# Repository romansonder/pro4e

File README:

########################################################################
# How to use git
########################################################################
First time you run git:
$ git clone https://github.com/romansonder/pro4e.git

$ git pull			# download the newest files from git

$ git add *			# select the files you want to upload
$ git commit			# write in your changes
$ git push			# upload your files to git

########################################################################
# Run the Makefiles on Windows:
########################################################################

#-----------------------------------------------------------------------
# Installation of cygwin
#-----------------------------------------------------------------------
Install cygwin from this site:
https://cygwin.com/install.html

Select a Download Site (mirror), if possible one in your country.

Select the following packages to be installed (allways newest version):

make: the Gnu version
git: Distributed version
texlive: TEX Live binaries
texlive-collection-latex
texlive-collection-latexextra
texlive-collection-langerman
texlive-collection-bibtexextra
texlive-collection-context
texlive-collection-fontsrecommended
texlive-collection-formatsextra
texlive-collection-pictures
texlive-collection-plaingeneric
texlive-collection-mathscience

#-----------------------------------------------------------------------
# Change to the Directory and run the Makefile
#-----------------------------------------------------------------------
open the cygwin terminal

clone the git repository
$ git clone http://..

change to the directory with the Makefile (use tab to autofill)
$ cd pro4e/documentation/02_technical_report/

run makefile
$ make

clean the directory from unused files
$ make clean

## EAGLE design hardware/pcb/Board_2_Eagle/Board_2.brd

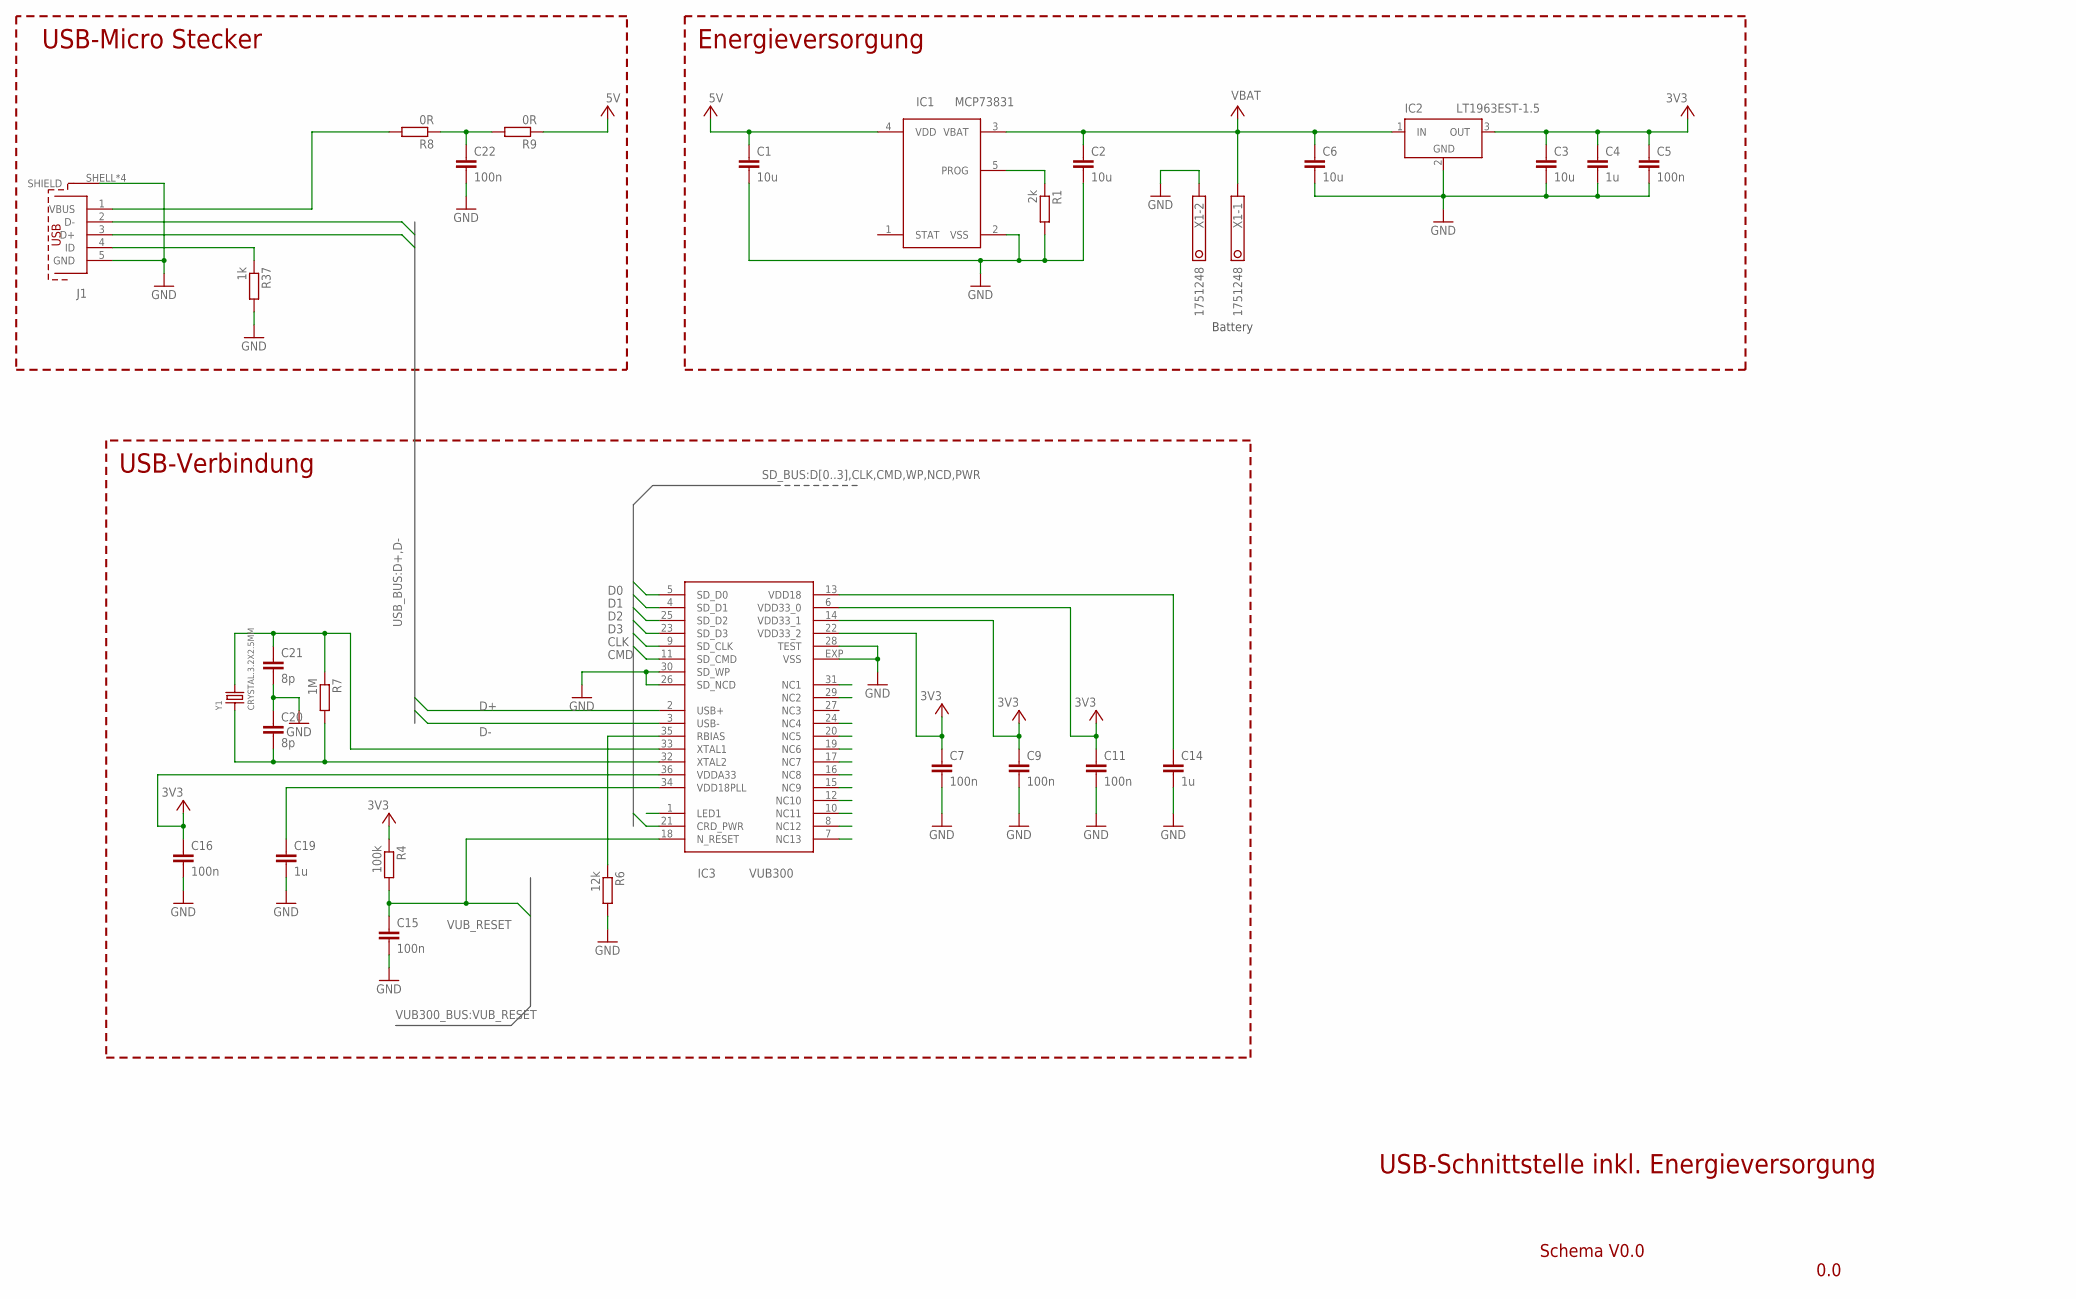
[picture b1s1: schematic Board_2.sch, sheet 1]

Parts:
C1, C2, C3, C6: 10u; C0805
C4: 1u; C0603
C5, C22: 100n; C0603
C7, C9, C11, C15, C16: 100n; C0402
C14, C19: 1u; C0402
C20, C21: 8p; C0402
IC1: MCP73831; SOT23-5
IC2: LT1963EST-1.5; SOT223
IC3: VUB300; QFN36-6X6
J1: 629105136821
R1: 2k; R0603
R4: 100k; R0402
R6: 12k; R0402
R7: 1M; R0402
R8, R9: 0R; R0603
R37: 1k; R0402
X1: 1751248
Y1: CRYSTAL.3.2X2.5MM; 3.2X2.5MM

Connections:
+3V3: C3.1, C4.1, C5.1, C7.1, C9.1, C11.1, C16.1, IC2.3 (OUT), IC3.6 (VDD33_0), IC3.14 (VDD33_1), IC3.22 (VDD33_2), IC3.36 (VDDA33), R4.1; also elsewhere on the board
+5V: C1.1, IC1.4 (VDD), R9.1
CLK: IC3.9 (SD_CLK); also elsewhere on the board
CMD: IC3.11 (SD_CMD); also elsewhere on the board
D0: IC3.5 (SD_D0); also elsewhere on the board
D1: IC3.4 (SD_D1); also elsewhere on the board
D2: IC3.25 (SD_D2); also elsewhere on the board
D3: IC3.23 (SD_D3); also elsewhere on the board
D+: IC3.2 (USB+), J1.3 (D+)
D-: IC3.3 (USB-), J1.2 (D-)
GND: C1.2, C2.2, C3.2, C4.2, C5.2, C6.2, C7.2, C9.2, C11.2, C14.2, C15.2, C16.2, C19.2, C20.1, C21.2, C22.2, IC1.2 (VSS), IC2.2 (GND), IC2.4 (GND), IC3.26 (SD_NCD), IC3.28 (TEST), IC3.30 (SD_WP), IC3.EXP (VSS), J1.5 (GND), J1.SHELL (SHIELD), J1.SHELL1 (SHIELD), J1.SHELL2 (SHIELD), J1.SHELL3 (SHIELD), R1.2, R6.2, R37.2, X1.2; also elsewhere on the board
unnamed: IC1.5 (PROG), R1.1
unnamed: J1.4 (ID), R37.1
unnamed: IC3.35 (RBIAS), R6.1
unnamed: J1.1 (VBUS), R8.2
unnamed: C20.2, IC3.32 (XTAL2), R7.2, Y1.1
unnamed: C21.1, IC3.33 (XTAL1), R7.1, Y1.3 (2)
unnamed: C22.1, R8.1, R9.2
PWR: IC3.21 (CRD_PWR); also elsewhere on the board
V+: C2.1, C6.1, IC1.3 (VBAT), IC2.1 (IN), X1.1; also elsewhere on the board
VDD18: C14.1, IC3.13 (VDD18)
VDD18PLL: C19.1, IC3.34 (VDD18PLL)
VUB_RESET: C15.1, IC3.18 (N_RESET), R4.2; also elsewhere on the board

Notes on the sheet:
Battery
USB-Micro Stecker
Energieversorgung
USB-Verbindung
Schema V0.0
0.0
USB-Schnittstelle inkl. Energieversorgung

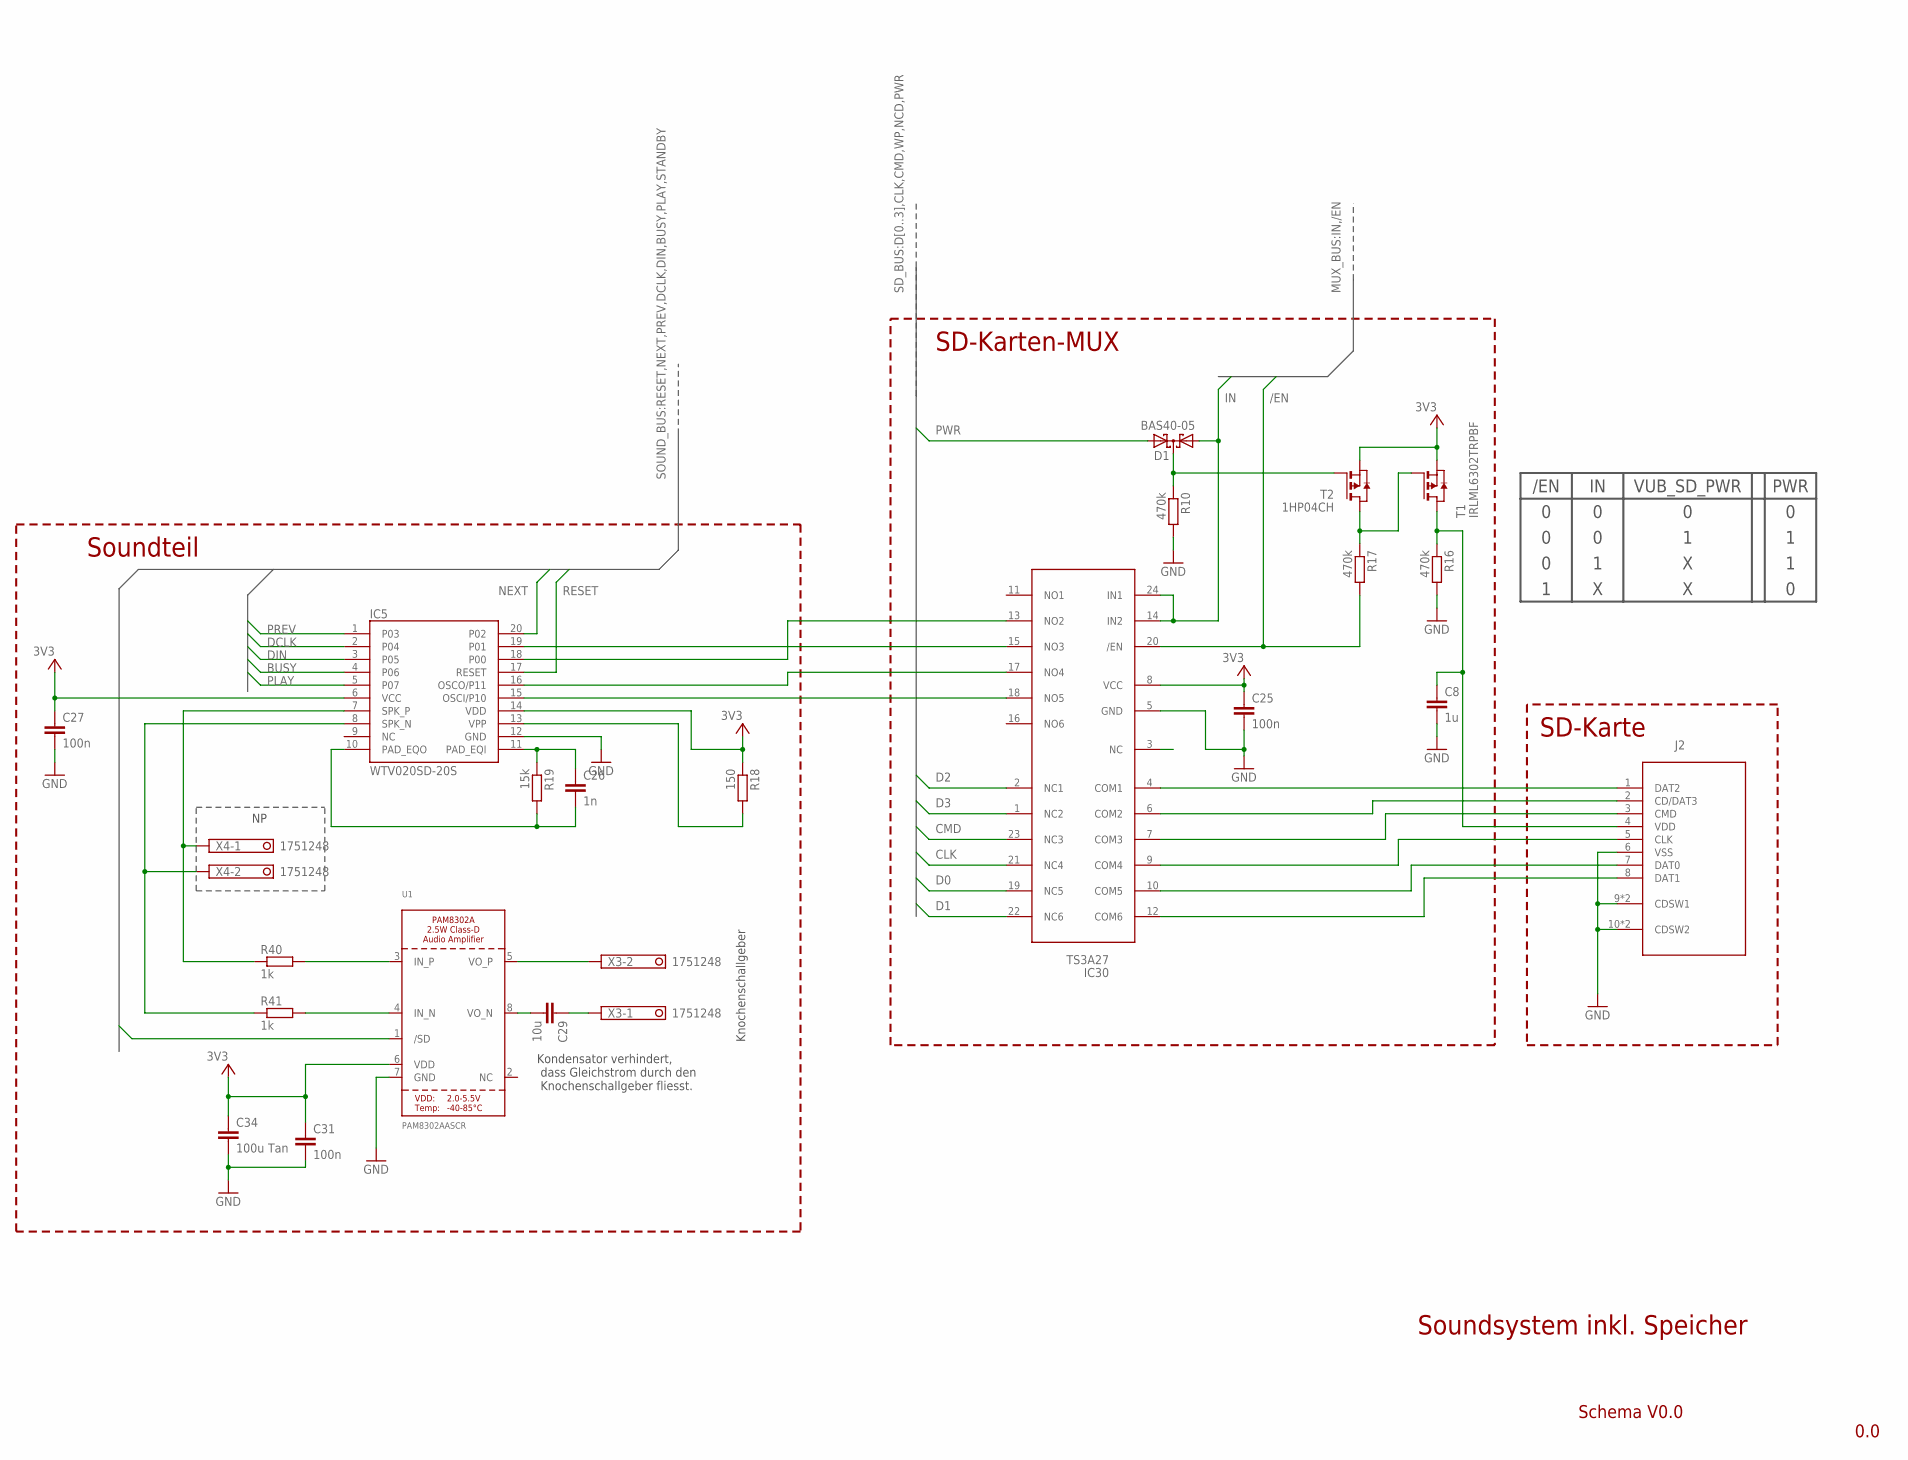
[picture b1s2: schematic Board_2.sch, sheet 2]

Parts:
C8: 1u; C0603
C25, C31: 100n; C0603
C26: 1n; C0402
C27: 100n; C0402
C29: 10u; C0603
C34: 100u Tan; C1206
D1: BAS40-05; SOT23
IC5: WTV020SD-20S; SSOP_20
IC30: TS3A27; TSSOP24
J2: 693071010811
R10, R16, R17: 470k; R0603
R18: 150; R0402
R19: 15k; R0402
R40, R41: 1k; R0402
T1: IRLML6302TRPBF; SOT-23
T2: 1HP04CH; SOT-23
U1: PAM8302AASCR; MSOP8_0.65MM
X3, X4: 1751248

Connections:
+3V3: C25.1, C27.1, C31.1, C34.1, IC5.6 (VCC), IC5.14 (VDD), IC30.8 (VCC), R18.1, T1.2 (S), T2.2 (S), U1.6 (VDD); also elsewhere on the board
/EN: IC30.20 (/EN), R17.2; also elsewhere on the board
BUSY: IC5.4 (P06); also elsewhere on the board
CLK: IC30.21 (NC4); also elsewhere on the board
CMD: IC30.23 (NC3); also elsewhere on the board
D0: IC30.19 (NC5); also elsewhere on the board
D1: IC30.22 (NC6); also elsewhere on the board
D2: IC30.2 (NC1); also elsewhere on the board
D3: IC30.1 (NC2); also elsewhere on the board
DCLK: IC5.2 (P04); also elsewhere on the board
DIN: IC5.3 (P05); also elsewhere on the board
GND: C8.2, C25.2, C27.2, C31.2, C34.2, IC5.12 (GND), IC30.5 (GND), J2.6 (VSS), J2.9 (CDSW1), J2.9-1 (CDSW1), J2.10 (CDSW2), J2.10-1 (CDSW2), R10.2, R16.2, U1.7 (GND); also elsewhere on the board
IN: D1.1 (A1), IC30.14 (IN2), IC30.24 (IN1); also elsewhere on the board
unnamed: R41.2, U1.4 (IN_N)
unnamed: IC5.19 (P01), IC30.15 (NO3)
unnamed: R40.2, U1.3 (IN_P)
unnamed: U1.5 (VO_P), X3.2
unnamed: C29.1, X3.1
unnamed: C29.2, U1.8 (VO_N)
unnamed: IC30.9 (COM4), J2.5 (CLK)
unnamed: IC5.13 (VPP), R18.2
unnamed: C26.1, IC5.11 (PAD_EQI), R19.1
unnamed: IC5.16 (OSCO/P11), IC30.17 (NO4)
unnamed: IC5.15 (OSCI/P10), IC30.18 (NO5)
unnamed: IC30.4 (COM1), J2.1 (DAT2)
unnamed: IC30.12 (COM6), J2.8 (DAT1)
unnamed: IC30.6 (COM2), J2.2 (CD/DAT3)
unnamed: R17.1, T1.3 (G), T2.1 (D)
unnamed: D1.3 (C), R10.1, T2.3 (G)
NCD1: C8.1, J2.4 (VDD), R16.1, T1.1 (D)
NEXT: IC5.20 (P02); also elsewhere on the board
PLAY: IC5.5 (P07); also elsewhere on the board
PREV: IC5.1 (P03); also elsewhere on the board
PWM: C26.2, IC5.10 (PAD_EQO), R19.2
PWR: D1.2 (A2); also elsewhere on the board
RESET: IC5.17 (RESET); also elsewhere on the board
SDCS: IC5.18 (P00), IC30.13 (NO2)
SDDI: IC30.7 (COM3), J2.3 (CMD)
SDDO: IC30.10 (COM5), J2.7 (DAT0)
SPK+: IC5.7 (SPK_P), R40.1, X4.1
SPK-: IC5.8 (SPK_N), R41.1, X4.2

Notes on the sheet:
SD-Karten-MUX
SD-Karte
Soundteil
Schema V0.0
0.0
Soundsystem inkl. Speicher
Knochenschallgeber
VUB_SD_PWR
/EN
PWR
Kondensator verhindert, dass Gleichstrom durch den Knochenschallgeber fliesst.

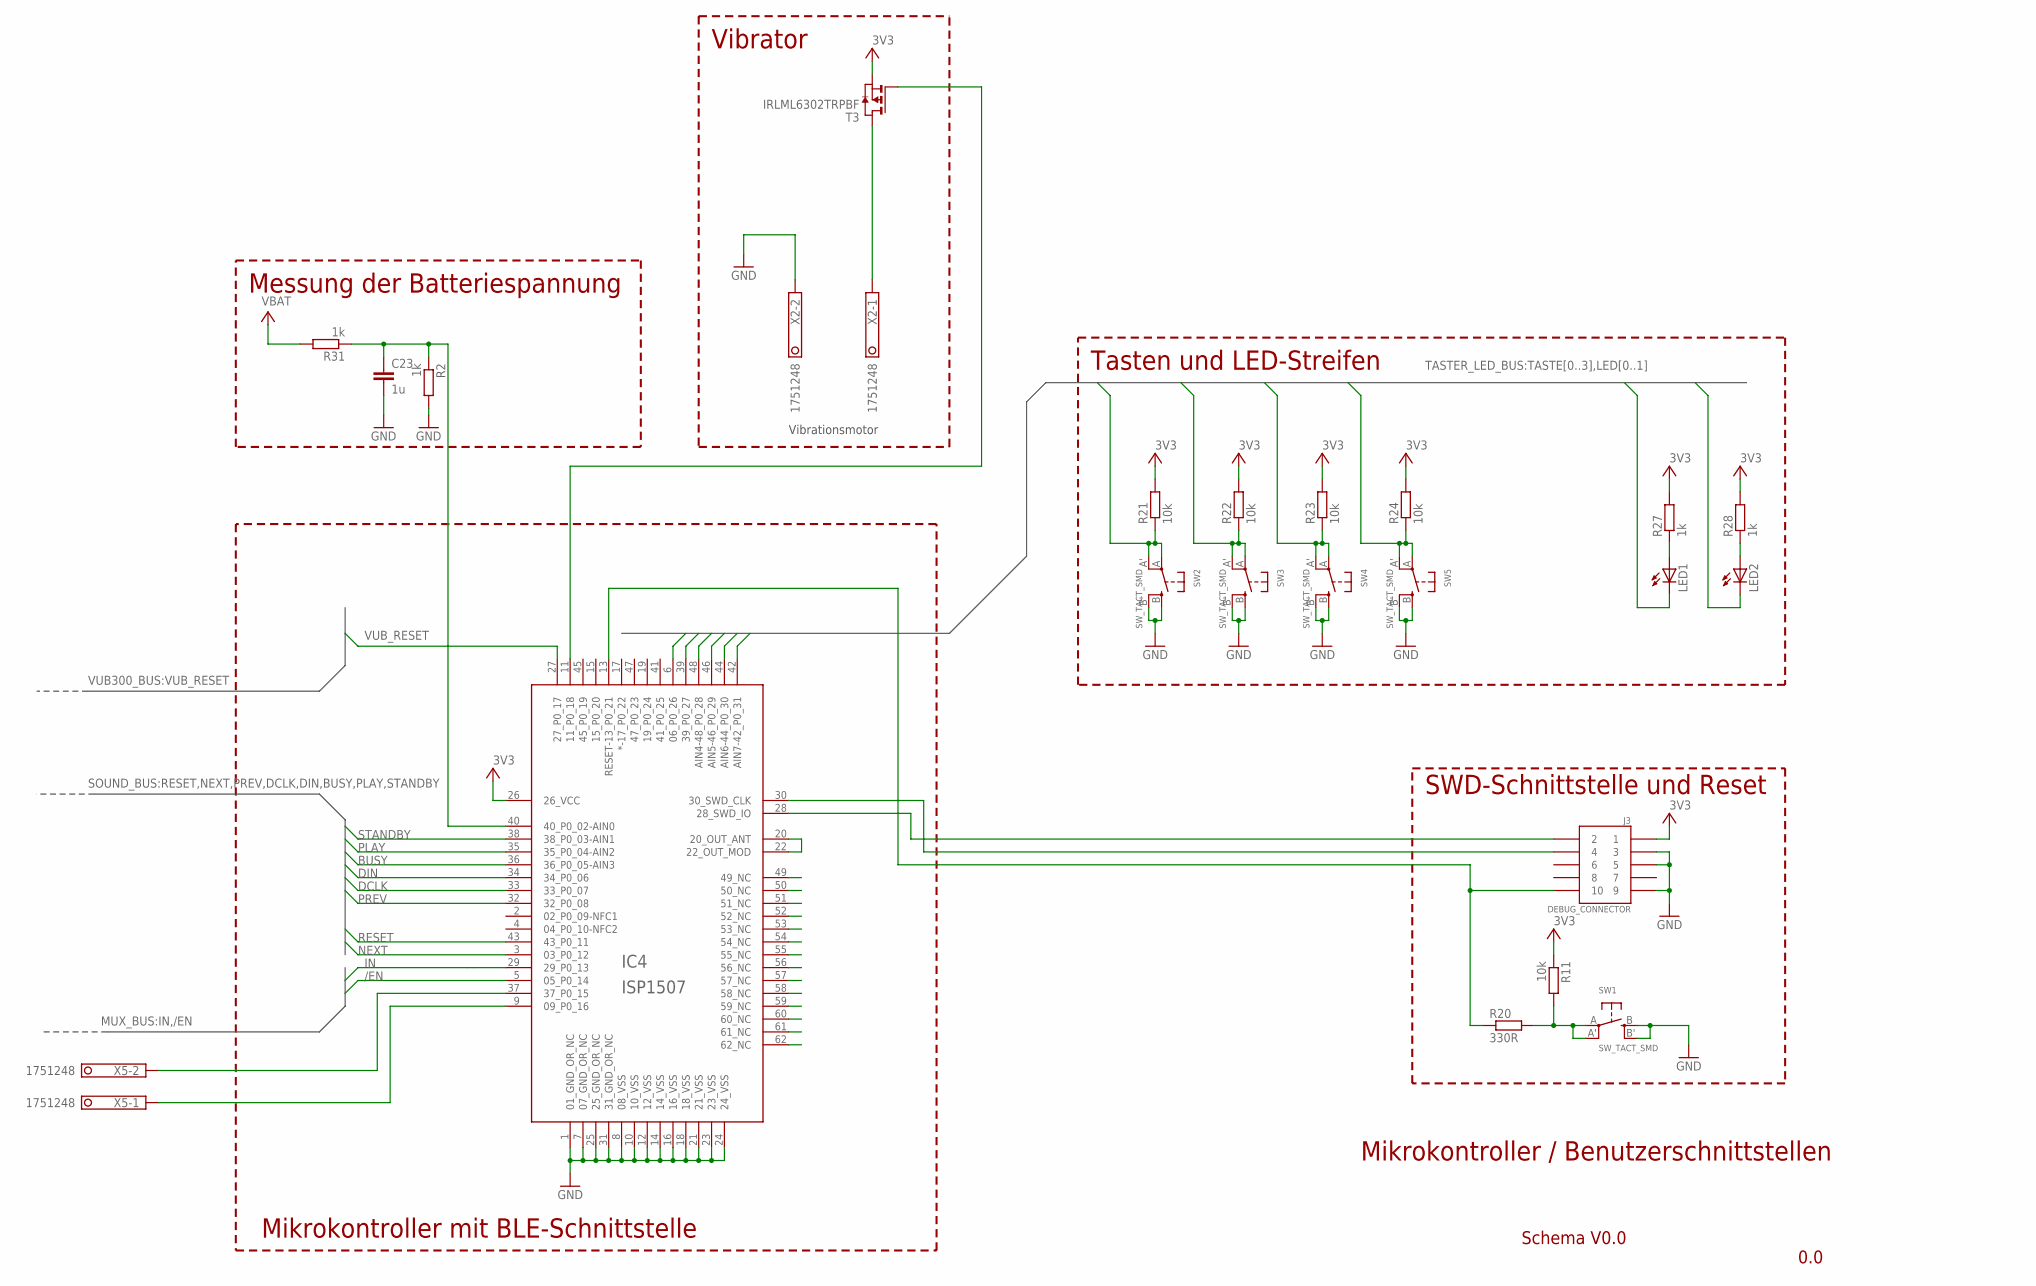
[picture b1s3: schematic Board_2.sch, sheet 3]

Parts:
C23: 1u; C0603
IC4: ISP1507
J3: DEBUG_CONNECTOR; HDRV127P5X2-10_N
LED1, LED2: LED_E; LED_1206
R2, R27, R28, R31: 1k; R0603
R11, R21, R22, R23, R24: 10k; R0603
R20: 330R; R0603
SW1, SW2, SW3, SW4, SW5: SW_TACT_SMD; EVQ-Q2
T3: IRLML6302TRPBF; SOT-23
X2, X5: 1751248

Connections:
+3V3: IC4.26 (26_VCC), J3.1, R11.1, R21.2, R22.2, R23.2, R24.2, R27.2, R28.2, T3.2 (S); also elsewhere on the board
/EN: IC4.5 (05_P0_14); also elsewhere on the board
BUSY: IC4.36 (36_P0_05-AIN3); also elsewhere on the board
DCLK: IC4.33 (33_P0_07); also elsewhere on the board
DIN: IC4.34 (34_P0_06); also elsewhere on the board
GND: C23.2, IC4.1 (01_GND_OR_NC), IC4.7 (07_GND_OR_NC), IC4.8 (08_VSS), IC4.10 (10_VSS), IC4.12 (12_VSS), IC4.14 (14_VSS), IC4.16 (16_VSS), IC4.18 (18_VSS), IC4.21 (21_VSS), IC4.23 (23_VSS), IC4.24 (24_VSS), IC4.25 (25_GND_OR_NC), IC4.31 (31_GND_OR_NC), J3.3, J3.5, J3.9, R2.2, SW1.B (S), SW1.B' (S1), SW2.B (S), SW2.B' (S1), SW3.B (S), SW3.B' (S1), SW4.B (S), SW4.B' (S1), SW5.B (S), SW5.B' (S1), X2.2; also elsewhere on the board
IN: IC4.29 (29_P0_13); also elsewhere on the board
LED0: IC4.39 (39_P0_27), LED1.C
LED1: IC4.6 (06_P0_26), LED2.C
unnamed: IC4.37 (37_P0_15), X5.2
unnamed: IC4.20 (20_OUT_ANT), IC4.22 (22_OUT_MOD)
unnamed: IC4.11 (11_P0_18), T3.3 (G)
unnamed: IC4.9 (09_P0_16), X5.1
unnamed: R11.2, R20.2, SW1.A, SW1.A' (P1)
unnamed: IC4.30 (30_SWD_CLK), J3.4
unnamed: IC4.28 (28_SWD_IO), J3.2
unnamed: LED1.A, R27.1
unnamed: C23.1, IC4.40 (40_P0_02-AIN0), R2.1, R31.1
unnamed: LED2.A, R28.1
unnamed: T3.1 (D), X2.1
unnamed: IC4.13 (RESET-13_P0_21), J3.10, R20.1
NEXT: IC4.3 (03_P0_12); also elsewhere on the board
PLAY: IC4.35 (35_P0_04-AIN2); also elsewhere on the board
PREV: IC4.32 (32_P0_08); also elsewhere on the board
RESET: IC4.43 (43_P0_11); also elsewhere on the board
STANDBY: IC4.38 (38_P0_03-AIN1)
TASTE0: IC4.42 (AIN7-42_P0_31), R21.1, SW2.A, SW2.A' (P1)
TASTE1: IC4.44 (AIN6-44_P0_30), R22.1, SW3.A, SW3.A' (P1)
TASTE2: IC4.46 (AIN5-46_P0_29), R23.1, SW4.A, SW4.A' (P1)
TASTE3: IC4.48 (AIN4-48_P0_28), R24.1, SW5.A, SW5.A' (P1)
V+: R31.2; also elsewhere on the board
VUB_RESET: IC4.27 (27_P0_17); also elsewhere on the board

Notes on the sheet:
Vibrationsmotor
Tasten und LED-Streifen
SWD-Schnittstelle und Reset
Vibrator
Messung der Batteriespannung
Mikrokontroller mit BLE-Schnittstelle
Schema V0.0
0.0
Mikrokontroller / Benutzerschnittstellen

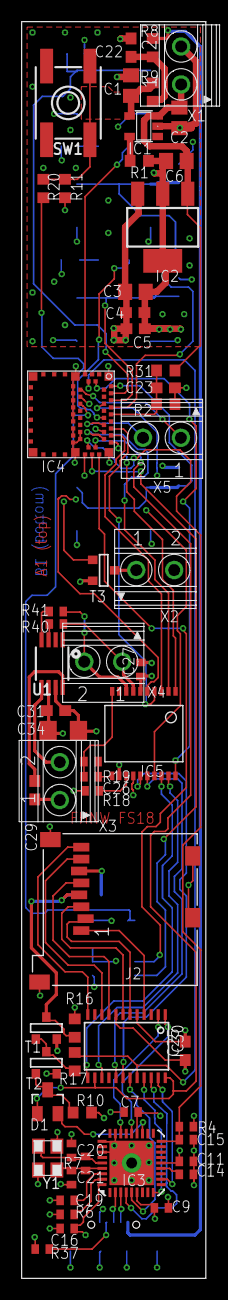
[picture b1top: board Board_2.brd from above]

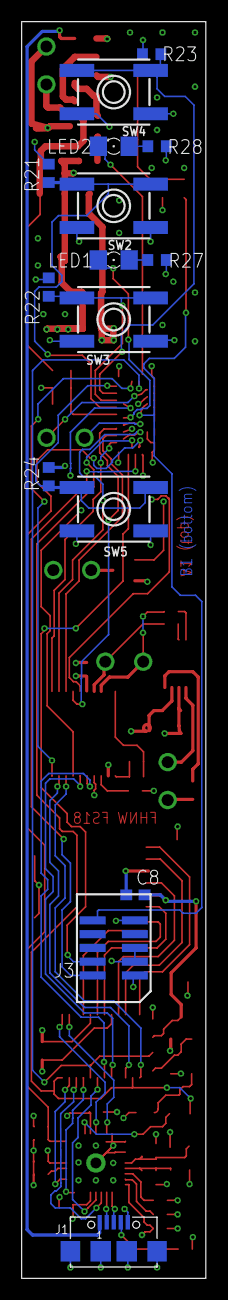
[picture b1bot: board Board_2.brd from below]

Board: 4 copper layers, 17.0 x 116.0 mm, 75 parts (15 on the bottom side), 73 nets.

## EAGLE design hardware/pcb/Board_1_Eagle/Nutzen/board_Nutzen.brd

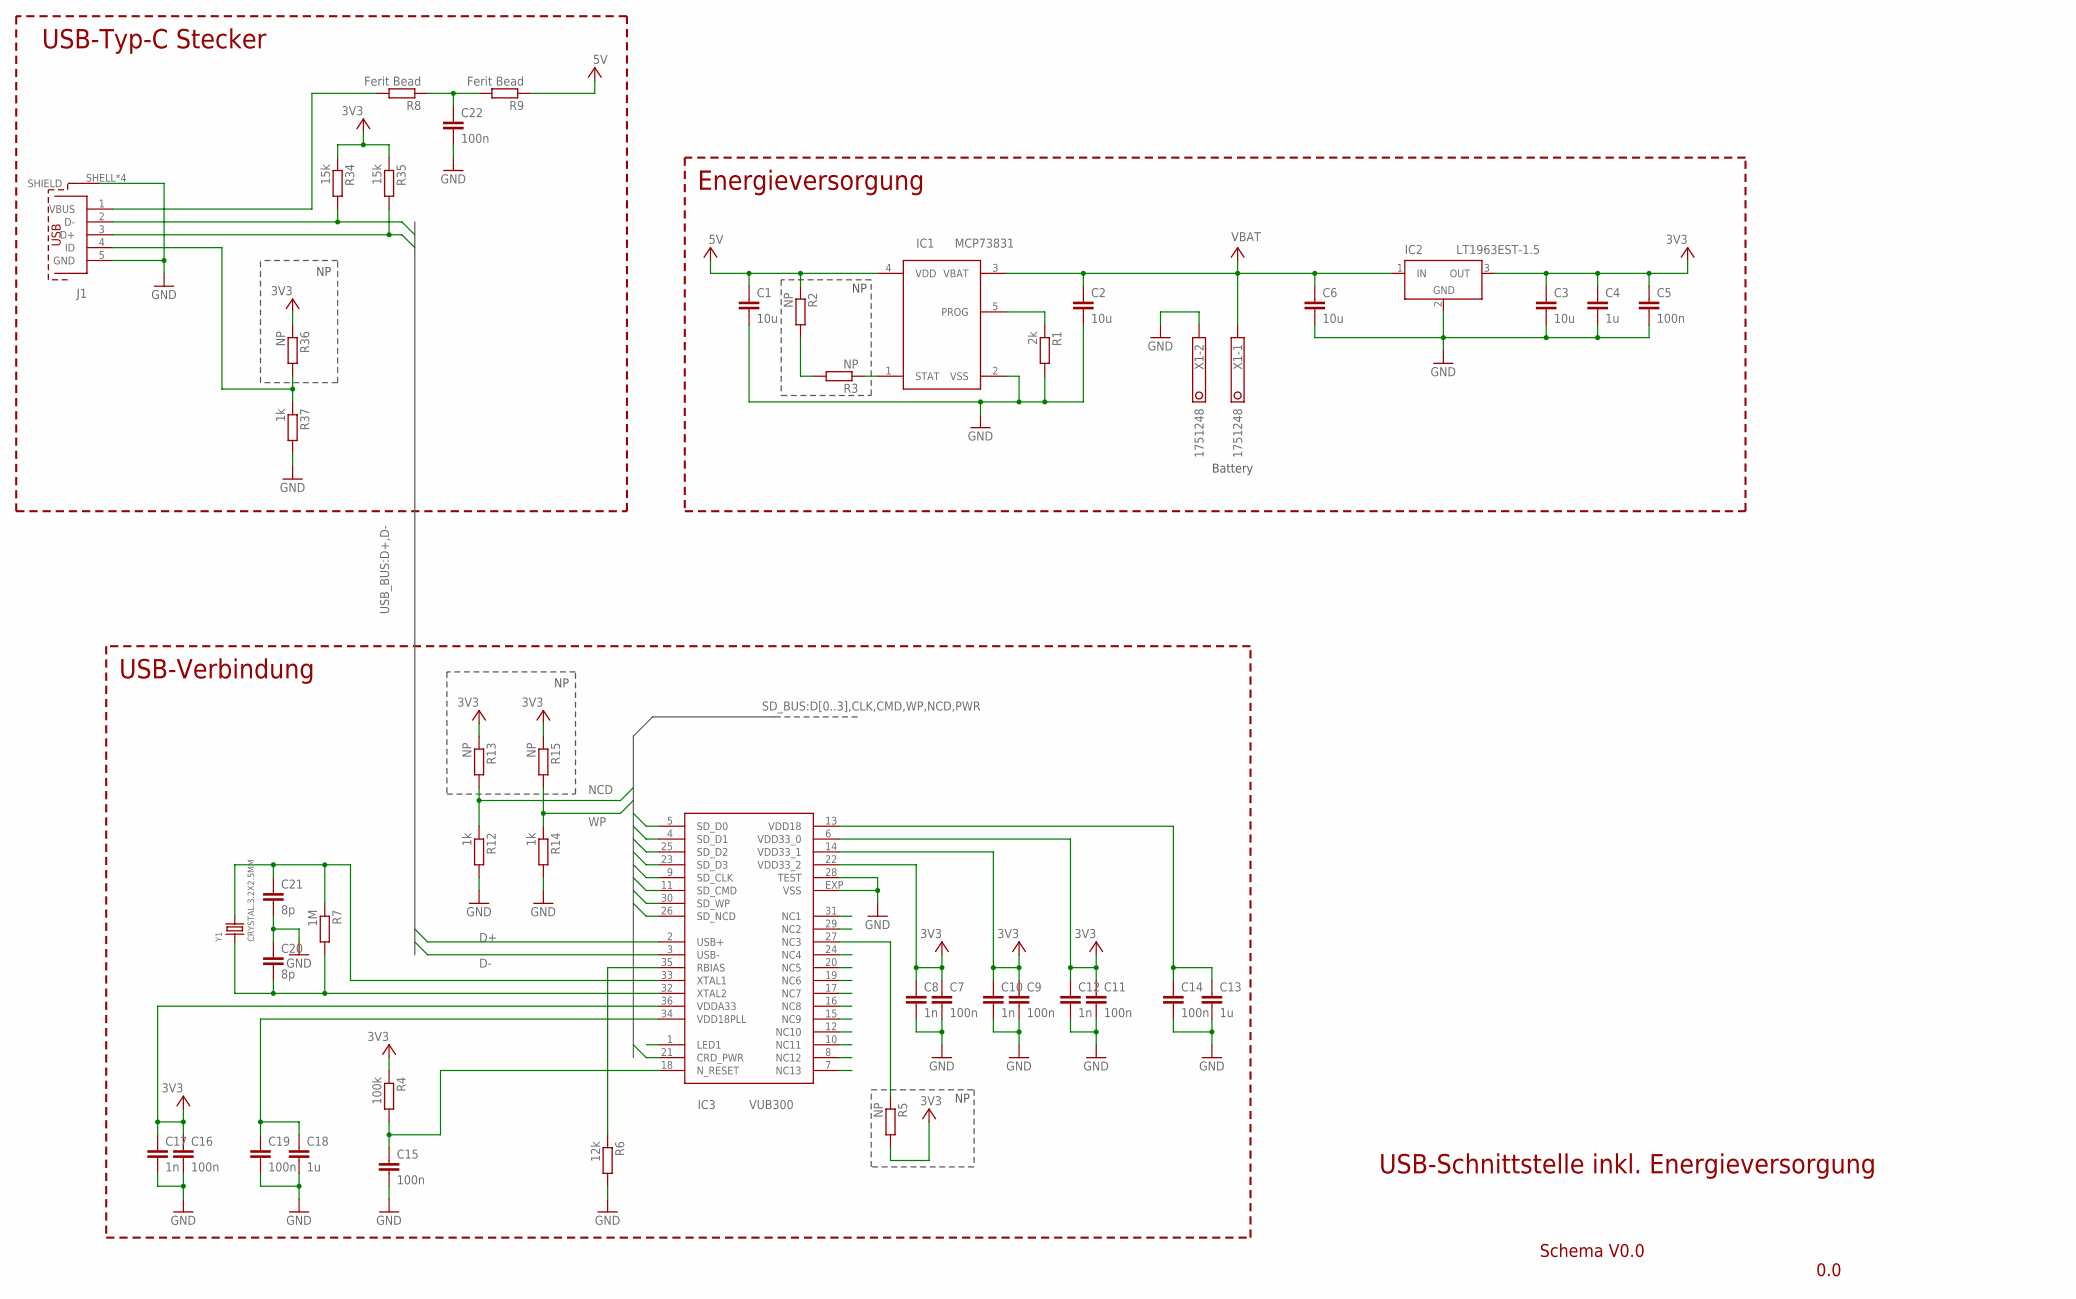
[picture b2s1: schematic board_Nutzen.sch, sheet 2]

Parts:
C1, C2, C3, C6: 10u; C0805
C4: 1u; C0603
C5, C22: 100n; C0603
C7, C9, C11, C14, C15, C16, C19: 100n; C0402
C8, C10, C12, C17: 1n; C0402
C13, C18: 1u; C0402
C20, C21: 8p; C0402
IC1: MCP73831; SOT23-5
IC2: LT1963EST-1.5; SOT223
IC3: VUB300; QFN36-6X6
J1: 629105136821
R1: 2k; R0603
R2, R3, R13, R15, R36: NP; R0603
R4: 100k; R0402
R5: NP; R0402
R6: 12k; R0402
R7: 1M; R0402
R8, R9: Ferit Bead; R0603
R12, R14, R37: 1k; R0603
R34, R35: 15k; R0402
X1: 1751248
Y1: CRYSTAL.3.2X2.5MM; 3.2X2.5MM

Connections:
+3V3: C3.1, C4.1, C5.1, C7.1, C8.1, C9.1, C10.1, C11.1, C12.1, C16.1, C17.1, IC2.3 (OUT), IC3.6 (VDD33_0), IC3.14 (VDD33_1), IC3.22 (VDD33_2), IC3.36 (VDDA33), R4.1, R5.2, R13.1, R15.1, R34.1, R35.1, R36.1; also elsewhere on the board
+5V: C1.1, IC1.4 (VDD), R2.1, R9.1; also elsewhere on the board
CLK: IC3.9 (SD_CLK); also elsewhere on the board
CMD: IC3.11 (SD_CMD); also elsewhere on the board
D0: IC3.5 (SD_D0); also elsewhere on the board
D1: IC3.4 (SD_D1); also elsewhere on the board
D2: IC3.25 (SD_D2); also elsewhere on the board
D3: IC3.23 (SD_D3); also elsewhere on the board
D+: IC3.2 (USB+), J1.3 (D+), R35.2; also elsewhere on the board
D-: IC3.3 (USB-), J1.2 (D-), R34.2; also elsewhere on the board
GND: C1.2, C2.2, C3.2, C4.2, C5.2, C6.2, C7.2, C8.2, C9.2, C10.2, C11.2, C12.2, C13.2, C14.2, C15.2, C16.2, C17.2, C18.2, C19.2, C20.1, C21.2, C22.2, IC1.2 (VSS), IC2.2 (GND), IC2.4 (GND), IC3.28 (TEST), IC3.EXP (VSS), J1.5 (GND), J1.SHELL (SHIELD), J1.SHELL1 (SHIELD), J1.SHELL2 (SHIELD), J1.SHELL3 (SHIELD), R1.2, R6.2, R12.2, R14.2, R37.2, X1.2; also elsewhere on the board
unnamed: IC1.5 (PROG), R1.1
unnamed: R2.2, R3.2
unnamed: IC1.1 (STAT), R3.1
unnamed: J1.4 (ID), R36.2, R37.1
unnamed: C15.1, IC3.18 (N_RESET), R4.2
unnamed: IC3.27 (NC3), R5.1
unnamed: IC3.35 (RBIAS), R6.1
unnamed: J1.1 (VBUS), R8.2
unnamed: C20.2, IC3.32 (XTAL2), R7.2, Y1.1
unnamed: C21.1, IC3.33 (XTAL1), R7.1, Y1.3 (2)
unnamed: C22.1, R8.1, R9.2
NCD: IC3.26 (SD_NCD), R12.1, R13.2; also elsewhere on the board
PWR: IC3.21 (CRD_PWR); also elsewhere on the board
V+: C2.1, C6.1, IC1.3 (VBAT), IC2.1 (IN), X1.1; also elsewhere on the board
VDD18: C13.1, C14.1, IC3.13 (VDD18); also elsewhere on the board
VDD18PLL: C18.1, C19.1, IC3.34 (VDD18PLL); also elsewhere on the board
WP: IC3.30 (SD_WP), R14.1, R15.2; also elsewhere on the board

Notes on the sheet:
Battery
USB-Typ-C Stecker
Energieversorgung
USB-Verbindung
Schema V0.0
0.0
USB-Schnittstelle inkl. Energieversorgung

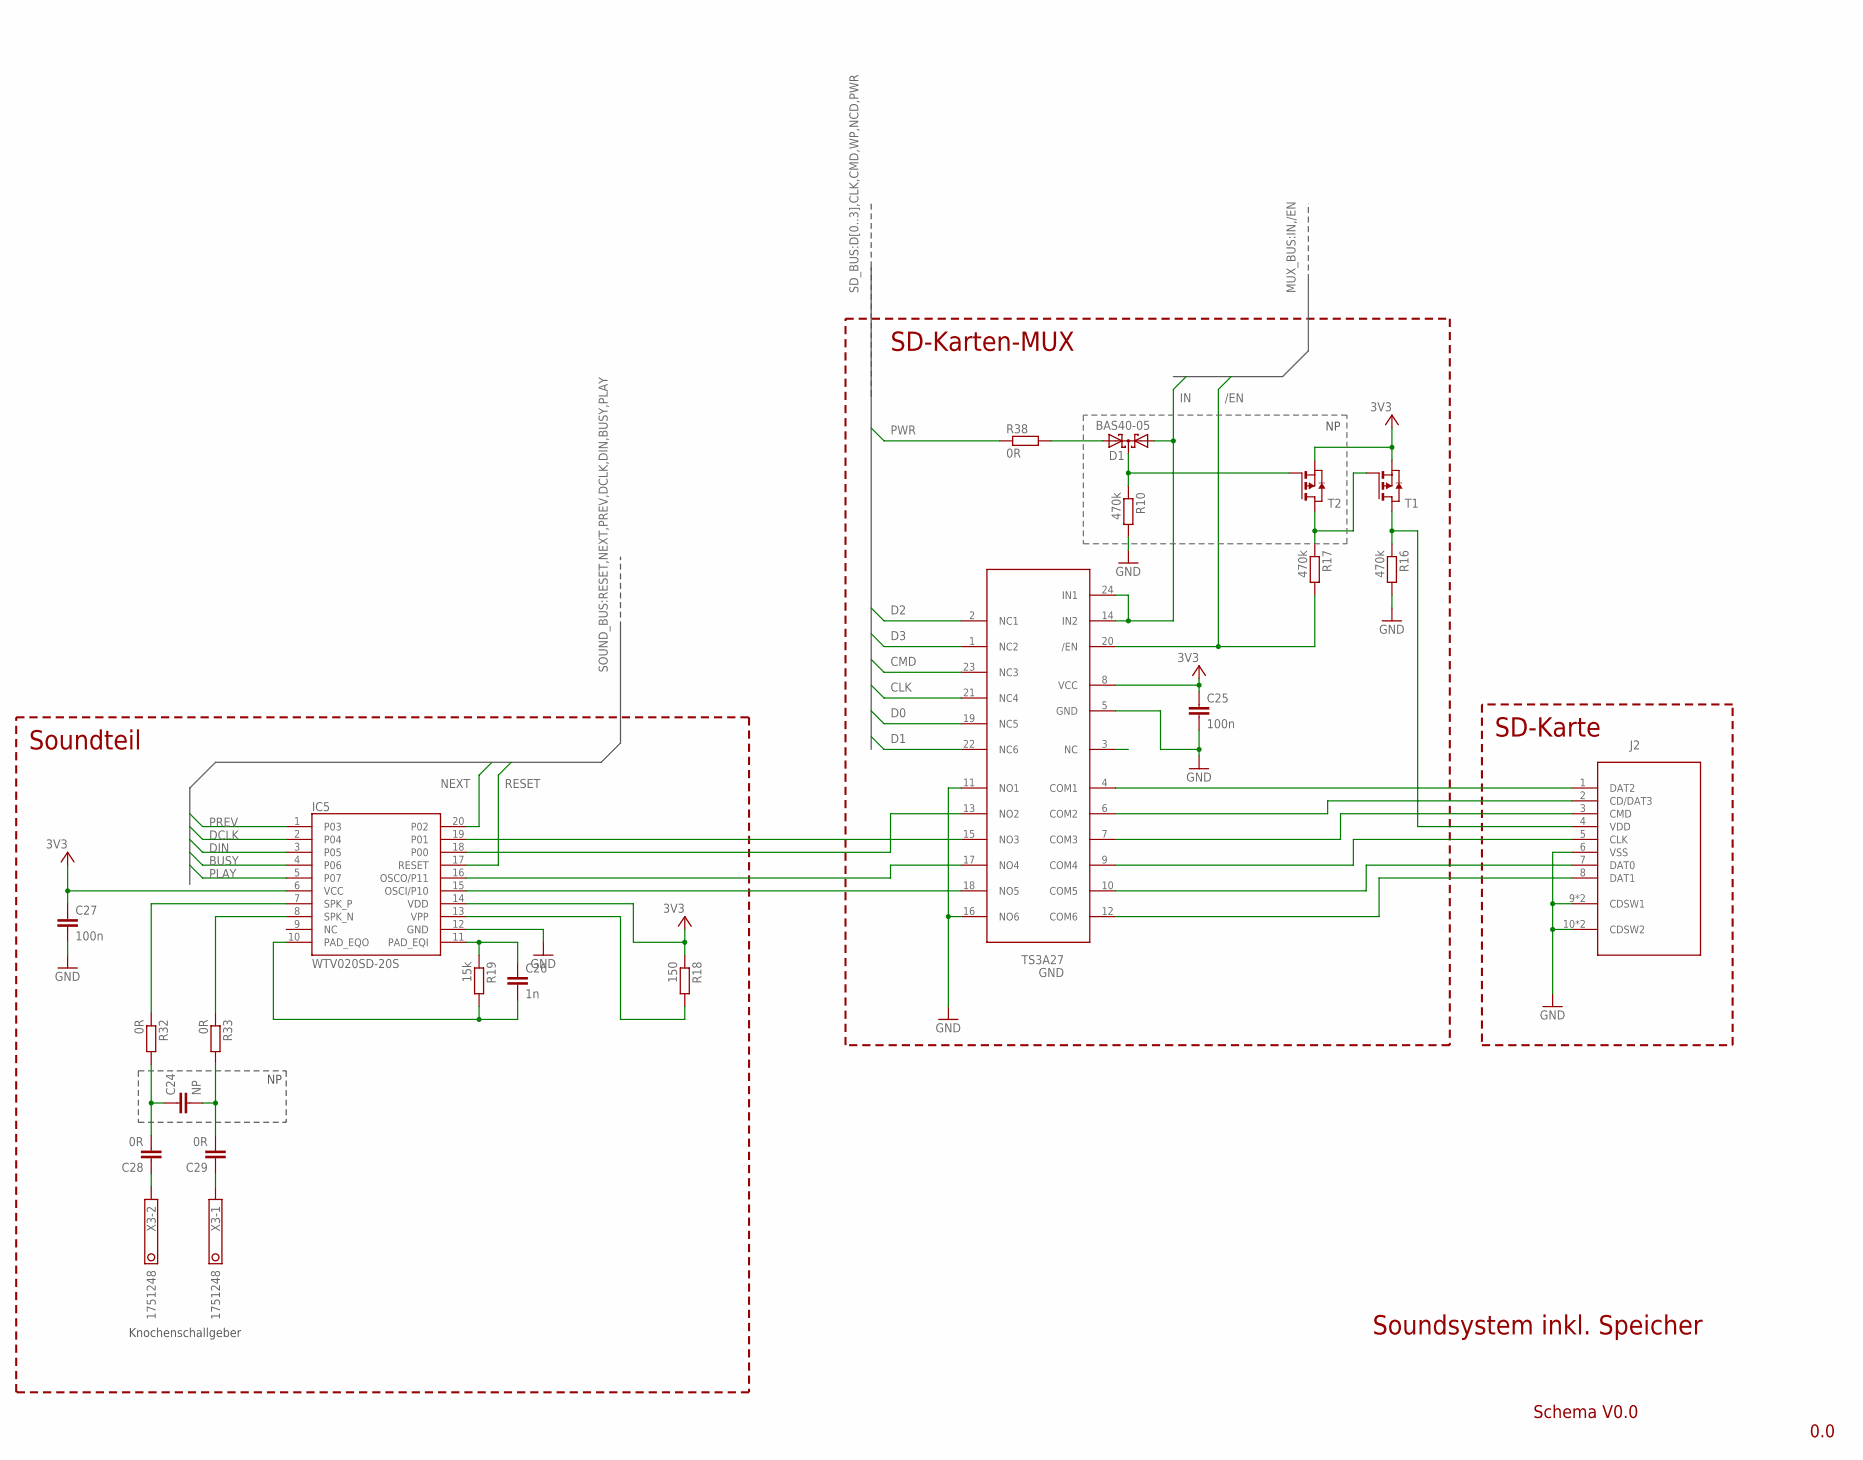
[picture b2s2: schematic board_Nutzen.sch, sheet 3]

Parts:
C24: NP; C0603
C25, C27: 100n; C0603
C26: 1n; C0603
C28, C29: 0R; C0603
D1: BAS40-05; SOT23
GND: TS3A27; TSSOP24
IC5: WTV020SD-20S; SSOP_20
J2: 693071010811
R10, R16, R17: 470k; R0603
R18: 150; R0603
R19: 15k; R0603
R32, R33: 0R; R0603
R38: 0R; MINI_MELF-0102W
T1, T2: PMOSSOT23; SOT-23
X3: 1751248

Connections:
+3V3: C25.1, C27.1, GND.8 (VCC), IC5.6 (VCC), IC5.14 (VDD), R18.1, T1.2 (S), T2.2 (S); also elsewhere on the board
/EN: GND.20 (/EN), R17.2; also elsewhere on the board
BUSY: IC5.4 (P06); also elsewhere on the board
CLK: GND.21 (NC4); also elsewhere on the board
CMD: GND.23 (NC3); also elsewhere on the board
D0: GND.19 (NC5); also elsewhere on the board
D1: GND.22 (NC6); also elsewhere on the board
D2: GND.2 (NC1); also elsewhere on the board
D3: GND.1 (NC2); also elsewhere on the board
DCLK: IC5.2 (P04); also elsewhere on the board
DIN: IC5.3 (P05); also elsewhere on the board
GND: C25.2, C27.2, GND.5 (GND), GND.11 (NO1), GND.16 (NO6), IC5.12 (GND), J2.6 (VSS), J2.9 (CDSW1), J2.9-1 (CDSW1), J2.10 (CDSW2), J2.10-1 (CDSW2), R10.2, R16.2; also elsewhere on the board
IN: D1.1 (A1), GND.14 (IN2), GND.24 (IN1); also elsewhere on the board
unnamed: D1.2 (A2), R38.2
unnamed: GND.15 (NO3), IC5.19 (P01)
unnamed: GND.9 (COM4), J2.5 (CLK)
unnamed: IC5.13 (VPP), R18.2
unnamed: C26.1, IC5.11 (PAD_EQI), R19.1
unnamed: GND.17 (NO4), IC5.16 (OSCO/P11)
unnamed: GND.18 (NO5), IC5.15 (OSCI/P10)
unnamed: GND.4 (COM1), J2.1 (DAT2)
unnamed: GND.12 (COM6), J2.8 (DAT1)
unnamed: GND.6 (COM2), J2.2 (CD/DAT3)
unnamed: R17.1, T1.3 (G), T2.1 (D)
unnamed: D1.3 (C), R10.1, T2.3 (G)
unnamed: C28.1, X3.2
unnamed: C29.1, X3.1
unnamed: C24.2, C29.2, R33.2
unnamed: C24.1, C28.2, R32.2
NCD1: J2.4 (VDD), R16.1, T1.1 (D)
NEXT: IC5.20 (P02); also elsewhere on the board
PLAY: IC5.5 (P07); also elsewhere on the board
PREV: IC5.1 (P03); also elsewhere on the board
PWM: C26.2, IC5.10 (PAD_EQO), R19.2
PWR: R38.1; also elsewhere on the board
RESET: IC5.17 (RESET); also elsewhere on the board
SDCS: GND.13 (NO2), IC5.18 (P00)
SDDI: GND.7 (COM3), J2.3 (CMD)
SDDO: GND.10 (COM5), J2.7 (DAT0)
SPK+: IC5.7 (SPK_P), R32.1
SPK-: IC5.8 (SPK_N), R33.1

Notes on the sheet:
SD-Karten-MUX
SD-Karte
Soundteil
Schema V0.0
0.0
Soundsystem inkl. Speicher
Knochenschallgeber

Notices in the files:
parts and their libraries:
SparkFun-DigitalIC: Licensing: CC v3.0 Share-Alike You are welcome to use this library for commercial purposes.
InputOutputIO: Copyright: Würth Elektronik
